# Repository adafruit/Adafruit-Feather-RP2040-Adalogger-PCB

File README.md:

## Adafruit Feather RP2040 Adalogger - 8MB Flash with microSD Card - STEMMA QT / Qwiic PCB

<a href="http://www.adafruit.com/products/5980"><br/>
Click here to purchase one from the Adafruit shop</a>

PCB files for the Adafruit Feather RP2040 Adalogger - 8MB Flash with microSD Card - STEMMA QT / Qwiic. 

Format is EagleCAD schematic and board layout
* https://www.adafruit.com/product/5980

### Description

This is the Adafruit Feather RP2040 Adalogger - our take on an 'all-in-one' RP2040 data-logger (or data-reader) with built-in USB, battery charging, and a microSD holder ready to rock! [We have other boards in the Feather family, check'em out here](https://www.adafruit.com/feather)

The RP2040 Adalogger is the same size and shape as a Feather and is intended to make your next data logging or data reading project super easy. Micro SD card socket wired for SPI or SDIO? Yes! STEMMA QT / Qwiic connector for fast I2C? Of course! Neopixel? It's a-glowin' This board will work excellently with Arduino or CircuitPython/MicroPython for any data recording/retreiving projects.

At the Feather's heart is an RP2040 chip, clocked at 133 MHz and at 3.3V logic, the same one used in the Raspberry Pi Pico. This chip has a whopping 8MB of onboard QSPI FLASH and 264K of RAM! This makes it great for buffering and processing data before writing it to the SD card.

To make it easy to use for portable projects, we added a connector for any of our 3.7V Lithium polymer batteries and built-in battery charging. You don't need a battery, it will run just fine straight from the USB Type C connector. But, if you do have a battery, you can take it on the go, then plug in the USB to recharge. The Feather will automatically switch over to USB power when it's available.

Here're some handy specs! You get:

* Measures 2.0" x 0.9" x 0.28" (50.8mm x 22.8mm x 7mm) without headers soldered in
* Light as a (large?) feather - 6.3 grams
* RP2040 32-bit Cortex M0+ dual core running at ~133 MHz @ 3.3V logic and power
* 264 KB RAM
* 8 MB SPI FLASH chip for storing files and CircuitPython/MicroPython code storage. No EEPROM
* Tons of GPIO! 21 x GPIO pins with following capabilities:
* Four 12-bit ADCs (one more than Pico)
* Two I2C, Two SPI, and two UART peripherals, we label one for the 'main' interface in standard Feather locations
* 16 x PWM outputs - for servos, LEDs, etc
* Built-in 200mA+ lipoly charger with charging status indicator LED
* Pin #13 red LED for general purpose blinking
* RGB NeoPixel for full-color indication.
* MicroSD card holder for adding as much storage as you could possibly want for reading or writing. Connected to the 'second' SPI port on pins 18, 19, 20 and card select on 23. Optional card detect line can be connected to pin 15. For advanced hackers who want to use 4-bit SDIO, we connect DAT1 and DAT2 to 21 and 22 - note we do not have Arduino or CircuitPython code for this mode.
* On-board STEMMA QT connector that lets you quickly connect any Qwiic, STEMMA QT or Grove I2C devices with no soldering!
* Both Reset button and Bootloader select button for quick restarts (no unplugging-replugging to relaunch code)
* USB Type C connector lets you access built-in ROM USB bootloader and serial port debugging
* 3.3V Power/enable pin
* 4 mounting holes
* 12 MHz crystal for perfect timing.
* 3.3V regulator with 500mA peak current output

Comes assembled and tested, with some header. You'll need a soldering iron to attach the header for installing onto your Feather. Stacking headers will let you put another FeatherWing on top. Lipoly battery, MicroSD card, and USB cable not included (but we do have lots of options in the shop if you'd like!)

### License

Adafruit invests time and resources providing this open source design, please support Adafruit and open-source hardware by purchasing products from [Adafruit](https://www.adafruit.com)!

Designed by Limor Fried/Ladyada for Adafruit Industries.

Creative Commons Attribution/Share-Alike, all text above must be included in any redistribution. 
See license.txt for additional details.

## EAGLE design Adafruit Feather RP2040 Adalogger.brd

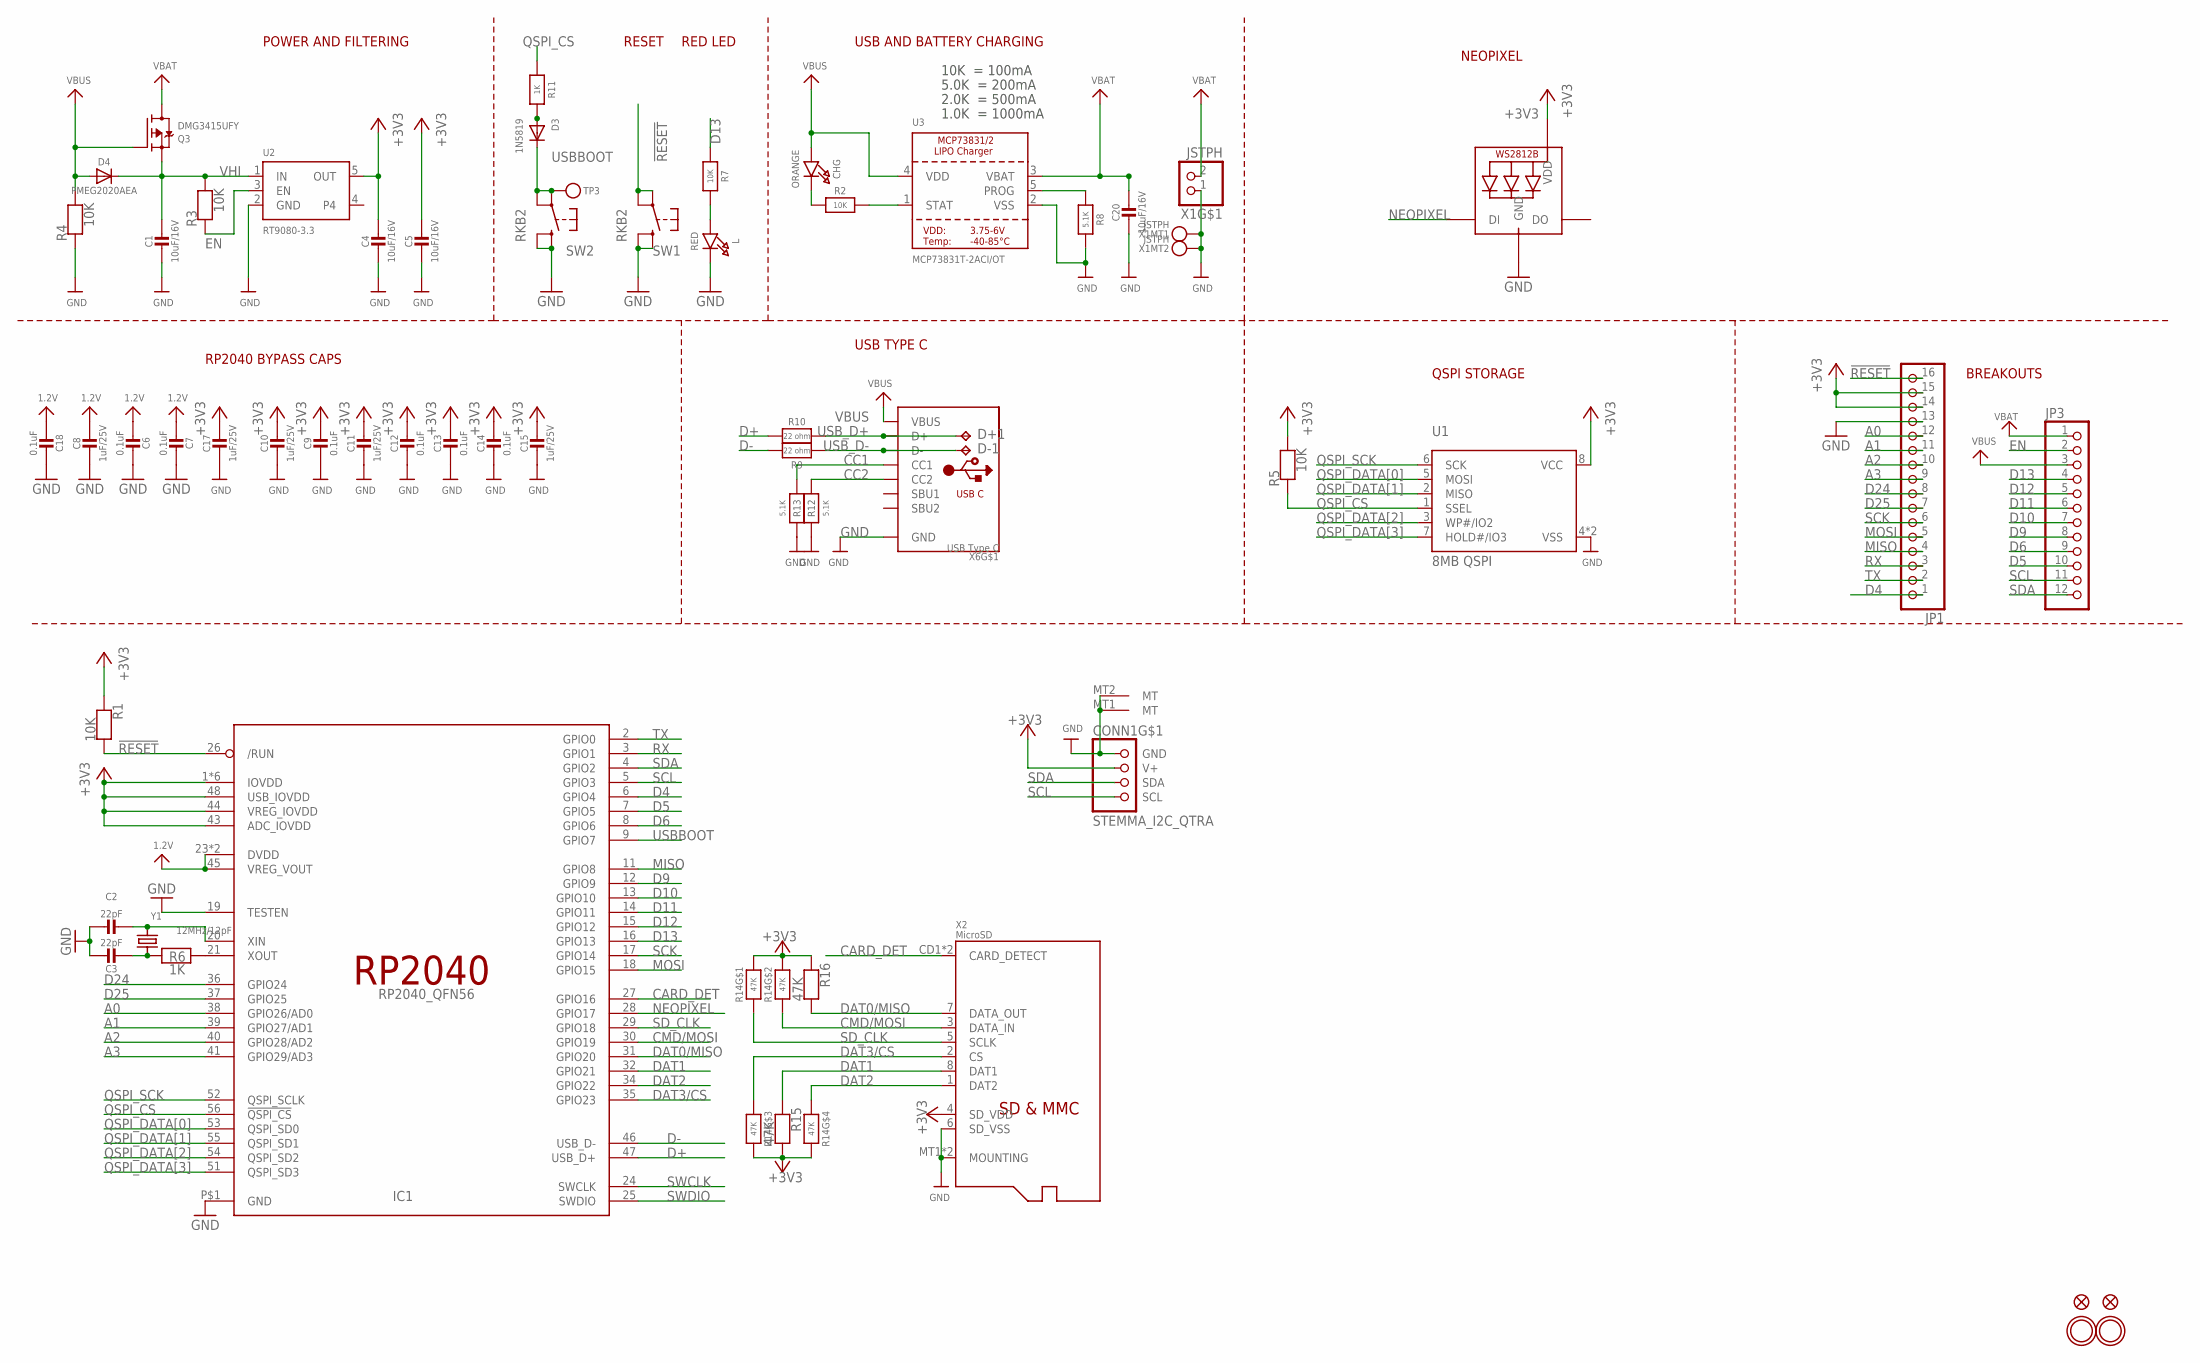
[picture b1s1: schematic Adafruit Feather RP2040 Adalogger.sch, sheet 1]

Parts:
C1, C4, C5, C20: 10uF/16V; 0805-NO
C2, C3: 22pF; _0402NO
C6, C7, C9, C12, C13, C14, C18: 0.1uF; _0402NO
C8, C10, C11, C15, C17: 1uF/25V; _0402NO
CHG: ORANGE; CHIPLED_0603_NOOUTLINE
CONN1: STEMMA_I2C_QTRA; JST_SH4_RA
D3: 1N5819; SOD-323_MINI
D4: PMEG2020AEA; SOD-323F
D+1: TPB1,27; B1,27
D-1: TPB1,27; B1,27
IC1: RP2040_QFN56; QFN56_7MM_REDUCEDEPAD
JP1: HEADER-1X16ROUND; 1X16_ROUND
JP3: HEADER-1X12; 1X12_ROUND
L: RED; CHIPLED_0603_NOOUTLINE
LED1: WS2812B_SK6805_1515; SK6805_1515
Q3: DMG3415UFY; DFN2015-3
R1, R2, R3, R4, R5, R7: 10K; _0402NO
R6, R11: 1K; _0402NO
R8, R12, R13: 5.1K; _0402NO
R9, R10: 22 ohm; _0402NO
R14: 47K; RESPACK_4X0603
R15, R16: 47K; _0402NO
SW1, SW2: RKB2; BTN_RKB2_4.6X2.8
TP3: TESTPOINTROUND1.5MMNO; TESTPOINT_ROUND_1.5MM_NO
U1: 8MB QSPI; USON8_4X4
U2: RT9080-3.3; SOT23-5; JLC_ROTATION 0
U3: MCP73831T-2ACI/OT; SOT23-5
U$31, U$32: MOUNTINGHOLE2.5; MOUNTINGHOLE_2.5_PLATED
U$34, U$35: FIDUCIAL_1MM
X1: JSTPH; JSTPH2_BATT
X2: MicroSD; MICROSD
X6: USB Type C; USB_C_CUSB31-CFM2AX-01-X
Y1: 12MHz/12pF; CRYSTAL_2.5X2

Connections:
1.2V: C6.2, C7.2, C8.1, C18.2, IC1.23 (DVDD), IC1.45 (VREG_VOUT), IC1.50 (DVDD)
!RESET: IC1.26 (/RUN), JP1.16, R1.2, SW1.A, SW1.A' (P1)
+3V3: C4.1, C5.1, C9.1, C10.1, C11.1, C12.1, C13.1, C14.1, C15.1, C17.1, CONN1.2 (V+), IC1.1 (IOVDD), IC1.10 (IOVDD), IC1.22 (IOVDD), IC1.33 (IOVDD), IC1.42 (IOVDD), IC1.43 (ADC_IOVDD), IC1.44 (VREG_IOVDD), IC1.48 (USB_IOVDD), IC1.49 (IOVDD), JP1.14, JP1.15, LED1.2 (VDD), R1.1, R5.2, R14.5 (2), R14.6 (2), R14.7 (2), R14.8 (2), R15.2, R16.1, U1.8 (VCC), U2.5 (OUT), X2.4 (SD_VDD)
A0: IC1.38 (GPIO26/AD0), JP1.12
A1: IC1.39 (GPIO27/AD1), JP1.11
A2: IC1.40 (GPIO28/AD2), JP1.10
A3: IC1.41 (GPIO29/AD3), JP1.9
CARD_DET: IC1.27 (GPIO16), X2.CD1 (CARD_DETECT), X2.CD2 (CARD_DETECT)
CC1: R13.2, X6.A5 (CC1)
CC2: R12.2, X6.B5 (CC2)
CMD/MOSI: IC1.30 (GPIO19), R14.2 (1), X2.3 (DATA_IN)
D4: IC1.6 (GPIO4), JP1.1
D5: IC1.7 (GPIO5), JP3.10
D6: IC1.8 (GPIO6), JP3.9
D9: IC1.12 (GPIO9), JP3.8
D10: IC1.13 (GPIO10), JP3.7
D11: IC1.14 (GPIO11), JP3.6
D12: IC1.15 (GPIO12), JP3.5
D13: IC1.16 (GPIO13), JP3.4, R7.1
D24: IC1.36 (GPIO24), JP1.8
D25: IC1.37 (GPIO25), JP1.7
D+: IC1.47 (USB_D+), R10.2
D-: IC1.46 (USB_D-), R9.2
DAT0/MISO: IC1.31 (GPIO20), R16.2, X2.7 (DATA_OUT)
DAT1: IC1.32 (GPIO21), R15.1, X2.8 (DAT1)
DAT2: IC1.34 (GPIO22), R14.4 (1), X2.1 (DAT2)
DAT3/CS: IC1.35 (GPIO23), R14.3 (1), X2.2 (CS)
EN: JP3.2, R3.1, U2.3 (EN)
GND: C1.2, C2.1, C3.1, C4.2, C5.2, C6.1, C7.1, C8.2, C9.2, C10.2, C11.2, C12.2, C13.2, C14.2, C15.2, C17.2, C18.1, C20.2, CONN1.1 (GND), CONN1.MT1 (MT), CONN1.MT2 (MT), IC1.19 (TESTEN), IC1.P$1 (GND), JP1.13, L.C, LED1.4 (GND), R4.1, R8.2, R12.1, R13.1, SW1.B (S), SW1.B' (S1), SW2.B (S), SW2.B' (S1), U1.4 (VSS), U1.PAD (VSS), U2.2 (GND), U3.2 (VSS), X1.1, X1.NC1, X1.NC2, X2.6 (SD_VSS), X2.MT1 (MOUNTING), X2.MT2 (MOUNTING), X6.A1B12 (GND), X6.B1A12 (GND)
MISO: IC1.11 (GPIO8), JP1.4
MOSI: IC1.18 (GPIO15), JP1.5
unnamed: CHG.C, R2.1
unnamed: L.A, R7.2
unnamed: R2.2, U3.1 (STAT)
unnamed: R8.1, U3.5 (PROG)
unnamed: C2.2, IC1.20 (XIN), Y1.3 (2)
unnamed: C3.2, R6.1, Y1.1
unnamed: IC1.21 (XOUT), R6.2
unnamed: D3.A, R11.2
NEOPIXEL: IC1.28 (GPIO17), LED1.1 (DI)
QSPI_CS: IC1.56 (!QSPI_CS), R5.1, R11.1, U1.1 (SSEL)
QSPI_DATA[0]: IC1.53 (QSPI_SD0), U1.5 (MOSI)
QSPI_DATA[1]: IC1.55 (QSPI_SD1), U1.2 (MISO)
QSPI_DATA[2]: IC1.54 (QSPI_SD2), U1.3 (WP#/IO2)
QSPI_DATA[3]: IC1.51 (QSPI_SD3), U1.7 (HOLD#/IO3)
QSPI_SCK: IC1.52 (QSPI_SCLK), U1.6 (SCK)
RX: IC1.3 (GPIO1), JP1.3
SCK: IC1.17 (GPIO14), JP1.6
SCL: CONN1.4 (SCL), IC1.5 (GPIO3), JP3.11
SDA: CONN1.3 (SDA), IC1.4 (GPIO2), JP3.12
SD_CLK: IC1.29 (GPIO18), R14.1, X2.5 (SCLK)
SWCLK: IC1.24 (SWCLK)
SWDIO: IC1.25 (SWDIO)
TX: IC1.2 (GPIO0), JP1.2
USBBOOT: D3.C, IC1.9 (GPIO7), SW2.A, SW2.A' (P1), TP3.P$1
USB_D+: D+1.TP, R10.1, X6.A6 (D+), X6.B6 (D+)
USB_D-: D-1.TP, R9.1, X6.A7 (D-), X6.B7 (D-)
VBAT: C20.1, JP3.1, Q3.3 (D), U3.3 (VBAT), X1.2
VBUS: CHG.A, D4.A, JP3.3, Q3.1 (G), R4.2, U3.4 (VDD), X6.A4B9 (VBUS), X6.B4A9 (VBUS)
VHI: C1.1, D4.C, Q3.2 (S), R3.2, U2.1 (IN)

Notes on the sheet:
POWER AND FILTERING
RESET
10K = 100mA
5.0K = 200mA
2.0K = 500mA
1.0K = 1000mA
USB AND BATTERY CHARGING
BREAKOUTS
RED LED
RP2040 BYPASS CAPS
USB TYPE C
QSPI STORAGE
NEOPIXEL

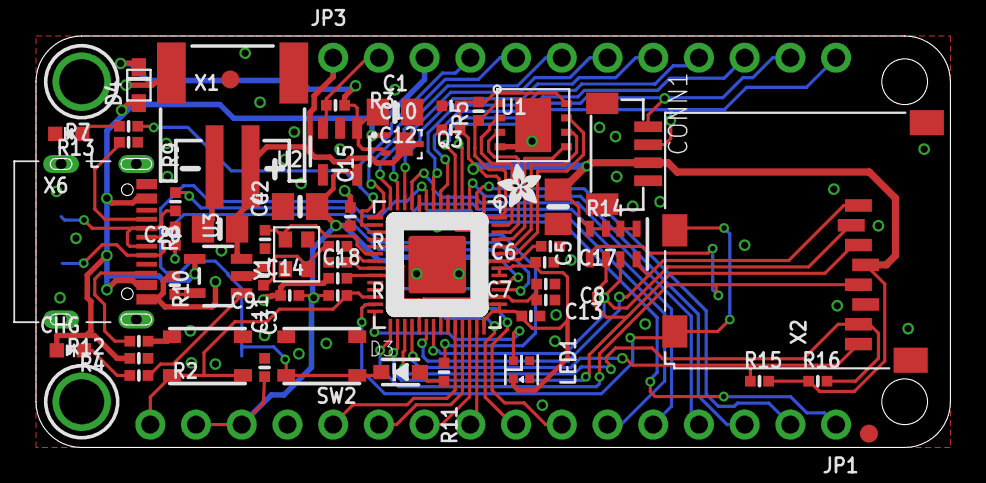
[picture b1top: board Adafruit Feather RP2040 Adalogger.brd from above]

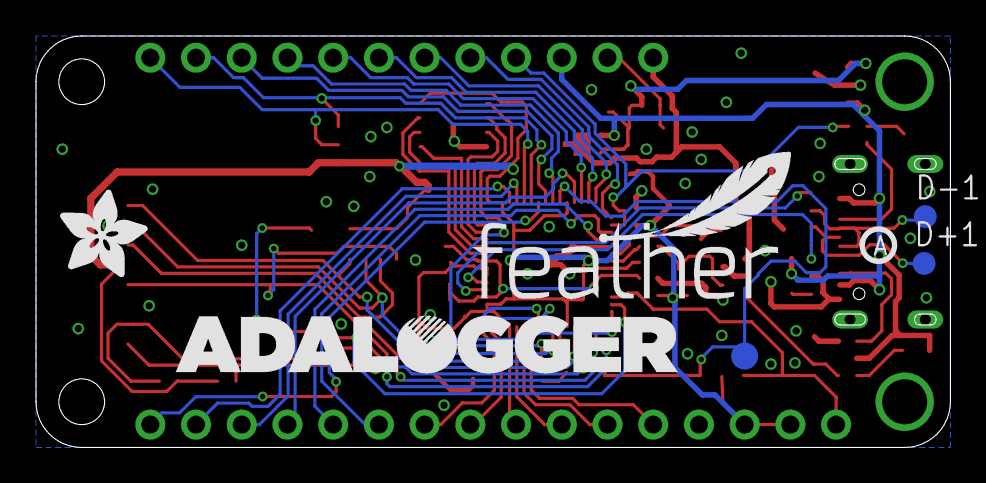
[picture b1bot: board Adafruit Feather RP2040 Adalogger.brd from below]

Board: 2 copper layers, 50.8 x 22.9 mm, 128 parts (37 on the bottom side), 58 nets.

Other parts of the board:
PLABEL62: PLABEL62
PLABEL63: PLABEL63
PLABEL64: PLABEL64
PLABEL65: PLABEL65
PLABEL66: PLABEL66
PLABEL67: PLABEL67
PLABEL68: PLABEL68
PLABEL69: PLABEL69
PLABEL70: PLABEL70
PLABEL71: PLABEL71
PLABEL72: PLABEL72
PLABEL73: PLABEL73
PLABEL74: PLABEL74
PLABEL75: PLABEL75
PLABEL76: PLABEL76
PLABEL77: PLABEL77
PLABEL78: PLABEL78
PLABEL79: PLABEL79
PLABEL80: PLABEL80
PLABEL81: PLABEL81
PLABEL82: PLABEL82
PLABEL83: PLABEL83
PLABEL84: PLABEL84
PLABEL85: PLABEL85
PLABEL86: PLABEL86
PLABEL87: PLABEL87
PLABEL88: PLABEL88
PLABEL89: PLABEL89
PLABEL90: PLABEL90
PLABEL91: PLABEL91
PLABEL92: PLABEL92
PLABEL93: PLABEL93
PLABEL94: PLABEL94
PLABEL95: PLABEL95
PLABEL96: PLABEL96
PLABEL97: PLABEL97
PLABEL98: PLABEL98
PLABEL99: PLABEL99
PLABEL100: PLABEL100
PLABEL101: PLABEL101
PLABEL102: PLABEL102
PLABEL103: PLABEL103
PLABEL104: PLABEL104
PLABEL105: PLABEL105
PLABEL106: PLABEL106
PLABEL107: PLABEL107
PLABEL108: PLABEL108
PLABEL109: PLABEL109
PLABEL110: PLABEL110
PLABEL111: PLABEL111
PLABEL112: PLABEL112
PLABEL113: PLABEL113
PLABEL114: PLABEL114
PLABEL115: PLABEL115
PLABEL116: PLABEL116
PLABEL117: PLABEL117
PLABEL118: PLABEL118
PLABEL119: PLABEL119
PLABEL120: PLABEL120
PLABEL121: PLABEL121
PLABEL122: PLABEL122
PLABEL123: PLABEL123
PLABEL124: PLABEL124
U$13: PCBFEAT-REV-040
U$28: ADALOGGER_LOGO
U$43: ADAFRUIT_2.5MM
U$46: FEATHERLOGO_MED
U$47: ADAFRUIT_5MM

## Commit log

2024-06-27 cookiecutter
2024-06-28 pretty
2024-06-28 add factory reset uf2
2025-09-24 Update prettypins to have correct battery terminal image

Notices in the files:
parts and their libraries:
microbuilder: This work is placed in the public domain, and may be freely used for commercial and non-commercial work with the following conditions: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
